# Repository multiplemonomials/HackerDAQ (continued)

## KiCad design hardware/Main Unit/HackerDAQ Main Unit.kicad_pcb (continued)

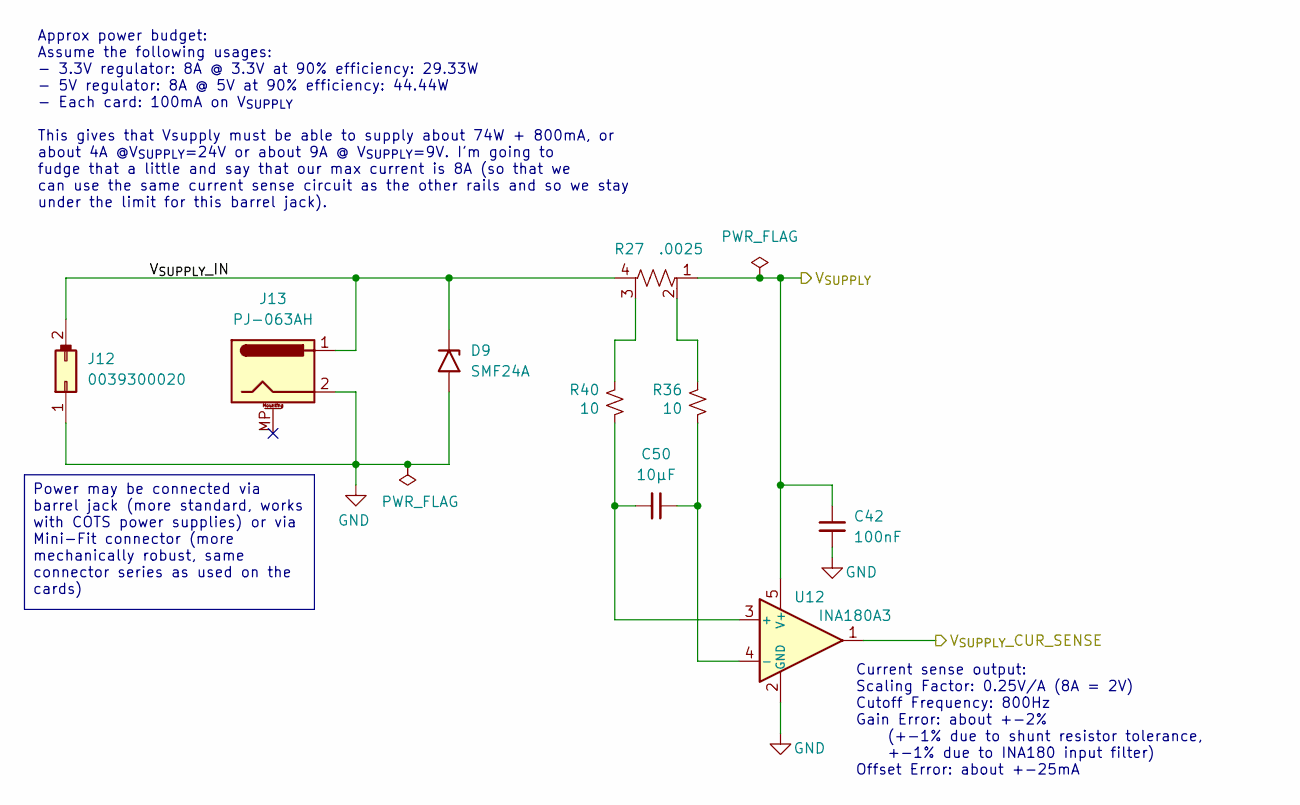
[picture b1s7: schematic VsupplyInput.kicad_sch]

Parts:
C42: 100nF; C_0603_1608Metric
C50: 10µF; C_1206_3216Metric
D9: SMF24A; D_SMF
J12: 0039300020; Molex_Mini-Fit_Jr_5569-02A2_2x01_P4.20mm_Horizontal
J13: PJ-063AH; BarrelJack_CUI_PJ-063AH_Horizontal
R27: .0025; D1FCP0612
R36, R40: 10; R_0603_1608Metric
U12: INA180A3; SOT-23-5

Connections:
/V_{SUPPLY} Input/V_{SUPPLY}_IN: D9.1 (A1), J12.2, J13.1, R27.4
/V_{SUPPLY}_CUR_SENSE: U12.1; also elsewhere on the board
unnamed: R27.2, R36.1
unnamed: R27.3, R40.1
unnamed: C50.2, R40.2, U12.3 (+)
unnamed: C50.1, R36.2, U12.4 (-)
V_{SUPPLY}: C42.1, R27.1, U12.5 (V+); also elsewhere on the board

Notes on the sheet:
Current sense output: Scaling Factor: 0.25V/A (8A = 2V) Cutoff Frequency: 800Hz Gain Error: about +-2% (+-1% due to shunt resistor tolerance, +-1% due to INA180 input filter) Offset Error: about +-25mA
Approx power budget: Assume the following usages: - 3.3V regulator: 8A @ 3.3V at 90% efficiency: 29.33W - 5V regulator: 8A @ 5V at 90% efficiency: 44.44W - Each card: 100mA on V_{SUPPLY} This gives that Vsupply must be able to supply about 74W + 800mA, or about 4A @V_{SUPPLY}=24V or about 9A @ V_{S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
Power may be connected via barrel jack (more standard, works with COTS power supplies) or via Mini-Fit connector (more mechanically robust, same connector series as used on the cards)

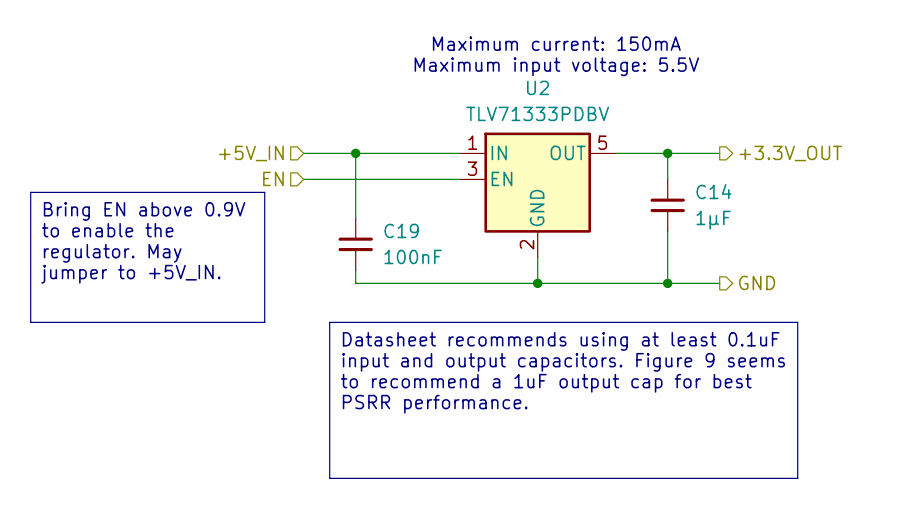
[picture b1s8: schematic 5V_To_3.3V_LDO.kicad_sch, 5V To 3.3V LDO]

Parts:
C14: 1µF; C_0603_1608Metric
C19: 100nF; C_0603_1608Metric
U2: TLV71333PDBV; SOT-23-5

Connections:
/~MCU_RST: U2.3 (EN); also elsewhere on the board

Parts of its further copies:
C3: 1µF; C_0603_1608Metric
C4: 100nF; C_0603_1608Metric

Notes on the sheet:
Maximum current: 150mA Maximum input voltage: 5.5V
Bring EN above 0.9V to enable the regulator. May jumper to +5V_IN.
Datasheet recommends using at least 0.1uF input and output capacitors. Figure 9 seems to recommend a 1uF output cap for best PSRR performance.

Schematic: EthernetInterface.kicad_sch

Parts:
C28, C35: 22µF; C_1210_3225Metric
C29, C31, C34, C44, C45: 100nF; C_0603_1608Metric
C33: 2.2µF; C_1206_3216Metric
D6: ESDS304; SOT-23-5
FB1, FB2: 300@100MHz; R_1206_3216Metric
J11: HFJ11-2450E-L21RL; RJ45_HALO_HFJ11-x2450E-LxxRL_Horizontal-Fixed3DModel
R14, R18: 10k; R_0603_1608Metric
R16, R17, R19, R20: 33; R_0603_1608Metric
R22: 6.49k; R_0603_1608Metric
R52, R53: 270; R_0603_1608Metric
R54: 4.7k; R_0603_1608Metric
U7: KSZ8081RND; QFN-24-1EP_4x4mm_P0.5mm_EP2.6x2.6mm

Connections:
/ETH_RMII.CRS_DV: R17.1, R18.2; also elsewhere on the board
/ETH_RMII.MDC: U7.11 (MDC); also elsewhere on the board
/ETH_RMII.MDIO: U7.10 (MDIO); also elsewhere on the board
/ETH_RMII.RMII_CLK: U7.8 (XI); also elsewhere on the board
/ETH_RMII.RXD0: R19.1; also elsewhere on the board
/ETH_RMII.RXD1: R20.1; also elsewhere on the board
/ETH_RMII.RX_ER: R14.2, R16.1; also elsewhere on the board
/ETH_RMII.TXD0: U7.20 (TXD0); also elsewhere on the board
/ETH_RMII.TXD1: U7.21 (TXD1); also elsewhere on the board
/ETH_RMII.TX_EN: U7.19 (TXEN); also elsewhere on the board
/EthernetInterface/ETH_MDI_RD+: D6.4 (K), J11.3 (RD+), U7.4 (RXP)
/EthernetInterface/ETH_MDI_RD-: D6.5 (K), J11.6 (RD-), U7.3 (RXM)
/EthernetInterface/ETH_MDI_TD+: D6.1 (K), J11.1 (TD+), U7.6 (TXP)
/EthernetInterface/ETH_MDI_TD-: D6.3 (K), J11.2 (TD-), U7.5 (TXM)
/EthernetInterface/KSZ_VDD1.2: C31.1, C33.1, U7.1 (VDD_1.2)
/EthernetInterface/~LED_GREEN: J11.12, R54.1, U7.23 (LED0/ANEN_SPEED)
/~ETH_SPEED_LED: J11.10; also elsewhere on the board
/~MCU_RST: U7.24 (~RST); also elsewhere on the board
unnamed: FB2.1, J11.8, J11.SH
unnamed: J11.9, R52.1
unnamed: J11.11, R53.1
unnamed: C45.1, J11.5 (RCT)
unnamed: C44.1, J11.4 (TCT)
unnamed: R17.2, U7.15 (CRS_DV/PHYAD[1:0])
unnamed: R22.2, U7.9 (REXT)
unnamed: R19.2, U7.13 (RXD0)
unnamed: R20.2, U7.12 (RXD1)
unnamed: R16.2, U7.17 (RXER)
unnamed: C34.1, C35.2, FB1.1, U7.2 (VDDA_3.3)

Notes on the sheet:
Green LED
Yellow LED
LED spec is 2.1V forward voltage @ 10mA. However, the KSZ8081 maxes out at 8mA of LED drive, and the MCU is similar. So, we will shoot for 5mA and assume that the forward voltage will decrease to around 2.0V
Per datasheet, RX_ER should be pulled low for correct operation (I guess it's an undocumented strapping pin?)
Ferrite bead per KSZ8081 reference design
CRS_DV pulled down to low and REF_CLK set high sets the PHY address to 4
Unfortunately there is only one LED pin on this PHY (it defaults to on for link up, flashing for activity). So, we will need to use the MCU to manually control the other (link speed) LED.
This part number of PHY is set up for MCUs like ours that can output a 50MHz clock. This clock is input to the PHY on the XI pin and is used both for the Ethernet signal generation and for the RMII interface. Look ma, no dedicated Ethernet crystal needed!

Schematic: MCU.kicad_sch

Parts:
C5, C7, C8, C10, C16, C17, C18, C19, C20, C21, C23, C26, C27, C36: 100nF; C_0603_1608Metric
C6: 2.2µF; C_1206_3216Metric
C9, C15, C24: 1µF; C_0603_1608Metric
C11: 220nF; C_0603_1608Metric
C13, C14: 10µF; C_1206_3216Metric
D1: AA3528QBS; AA3528
D2: AA3528SURSK; AA3528
D3: ASMB-MTB0-0B3A2; LED_Avago_PLCC4_3.2x2.8mm_CW
D4, D5: BAT54W; SOT-323_SC-70
J1: 3221-10-0300-00
J10: 1x8; PinSocket_1x08_P2.54mm_Vertical
J15: USB4105-GF-A; USB_C_Receptacle_GCT_USB4105-xx-A_16P_TopMnt_Horizontal-Ext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
L1: 1.5µH; L_1210_3225Metric
R1, R4, R7: 30; R_0603_1608Metric
R2, R3: 140; R_0603_1608Metric
R5, R6, R8, R23: 10k; R_0603_1608Metric
R9, R15: 2.2k; R_0603_1608Metric
R43, R44: 5.1k; R_0603_1608Metric
SW1, SW2: MJTP1243; SW_PUSH_1P1T_6x3.5mm_H4.3_APEM_MJTP1243
TP2: VCORE; TestPoint_THTPad_D2.5mm_Drill1.2mm
U5: MCXN547VKLT; LQFP-100-1EP_14x14mm_P0.5mm_EP6.9x6.9mm_Fixed3DModel
U13: USBLC6-2SC6; SOT-23-6
X1: 24.0000MHz; Oscillator_SMD_ECS_2520MV-xxx-xx-4Pin_2.5x2.0mm

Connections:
/+3.3V_CUR_SENSE: U5.22 (P4_0); also elsewhere on the board
/CARD_BUS_0_SPI.CARD_SEL: U5.15 (P2_1); also elsewhere on the board
/CARD_BUS_0_SPI.MISO: U5.19 (P2_5); also elsewhere on the board
/CARD_BUS_0_SPI.MOSI: U5.18 (P2_4); also elsewhere on the board
/CARD_BUS_0_SPI.SCLK: U5.17 (P2_3); also elsewhere on the board
/CARD_BUS_0_SPI.~CS0: U5.16 (P2_2); also elsewhere on the board
/CARD_BUS_0_SPI.~CS1: U5.14 (P2_0); also elsewhere on the board
/CARD_BUS_0_SPI.~CS2: U5.21 (P2_7); also elsewhere on the board
/CARD_BUS_0_SPI.~DRDY: U5.20 (P2_6); also elsewhere on the board
/CARD_BUS_1_SPI.CARD_SEL: U5.91 (P0_23); also elsewhere on the board
/CARD_BUS_1_SPI.MISO: U5.3 (P1_10); also elsewhere on the board
/CARD_BUS_1_SPI.MOSI: U5.1 (P1_8); also elsewhere on the board
/CARD_BUS_1_SPI.SCLK: U5.2 (P1_9); also elsewhere on the board
/CARD_BUS_1_SPI.~CS0: U5.4 (P1_11); also elsewhere on the board
/CARD_BUS_1_SPI.~CS1: U5.90 (P0_22); also elsewhere on the board
/CARD_BUS_1_SPI.~CS2: U5.92 (P1_0); also elsewhere on the board
/CARD_BUS_1_SPI.~DRDY: U5.93 (P1_1); also elsewhere on the board
/CARD_BUS_2_SPI.CARD_SEL: U5.64 (P3_13); also elsewhere on the board
/CARD_BUS_2_SPI.MISO: U5.61 (P3_16); also elsewhere on the board
/CARD_BUS_2_SPI.MOSI: U5.63 (P3_14); also elsewhere on the board
/CARD_BUS_2_SPI.SCLK: U5.62 (P3_15); also elsewhere on the board
/CARD_BUS_2_SPI.~CS0: U5.60 (P3_17); also elsewhere on the board
/CARD_BUS_2_SPI.~CS1: U5.57 (P3_20); also elsewhere on the board
/CARD_BUS_2_SPI.~CS2: U5.56 (P3_21); also elsewhere on the board
/CARD_BUS_2_SPI.~DRDY: U5.75 (P3_0); also elsewhere on the board
/CARD_BUS_3_SPI.CARD_SEL: U5.50 (P5_2); also elsewhere on the board
/CARD_BUS_3_SPI.MISO: U5.69 (P3_9); also elsewhere on the board
/CARD_BUS_3_SPI.MOSI: U5.70 (P3_8); also elsewhere on the board
/CARD_BUS_3_SPI.SCLK: U5.71 (P3_7); also elsewhere on the board
/CARD_BUS_3_SPI.~CS0: U5.65 (P3_12); also elsewhere on the board
/CARD_BUS_3_SPI.~CS1: U5.78 (P0_2); also elsewhere on the board
/CARD_BUS_3_SPI.~CS2: U5.79 (P0_3); also elsewhere on the board
/CARD_BUS_3_SPI.~DRDY: U5.51 (P5_3); also elsewhere on the board
/Card Bus Connectors0/~RESET: U5.27 (P4_5); also elsewhere on the board
/Card Bus Connectors0/~SYNC: U5.28 (P4_6); also elsewhere on the board
/DBG_UART.MCU_RX: U5.35 (P4_12); also elsewhere on the board
/DBG_UART.MCU_TX: U5.36 (P4_13); also elsewhere on the board
/ETH_RMII.CRS_DV: U5.6 (P1_13); also elsewhere on the board
/ETH_RMII.MDC: U5.94 (P1_2); also elsewhere on the board
/ETH_RMII.MDIO: R15.2, U5.95 (P1_3); also elsewhere on the board
/ETH_RMII.RMII_CLK: U5.97 (P1_4); also elsewhere on the board
/ETH_RMII.RXD0: U5.7 (P1_14); also elsewhere on the board
/ETH_RMII.RXD1: U5.8 (P1_15); also elsewhere on the board
/ETH_RMII.RX_ER: U5.5 (P1_12); also elsewhere on the board
/ETH_RMII.TXD0: U5.99 (P1_6); also elsewhere on the board
/ETH_RMII.TXD1: U5.100 (P1_7); also elsewhere on the board
/ETH_RMII.TX_EN: U5.98 (P1_5); also elsewhere on the board
/MCU/+5V_CUR_SENSE: U5.23 (P4_1); also elsewhere on the board
/MCU/CLK_24MHZ: U5.10 (EXTAL48M/P1_31), X1.3 (OUT)
/MCU/ERROR_LED: R2.2, U5.26 (P4_4)
/MCU/MCU_P0_4: J10.1, U5.80 (P0_4)
/MCU/MCU_P0_5: J10.2, U5.81 (P0_5)
/MCU/MCU_P0_16: J10.3, U5.84 (P0_16)
/MCU/MCU_P0_17: J10.4, U5.85 (P0_17)
/MCU/MCU_P0_18: J10.5, U5.86 (P0_18)
/MCU/MCU_P0_19: J10.6, U5.87 (P0_19)
/MCU/MCU_P0_20: J10.7, U5.88 (P0_20)
/MCU/MCU_P0_21: J10.8, U5.89 (P0_21)
/MCU/PREFILT_USBMCU_D+: J15.A6 (D+), J15.B6 (D+), U13.3 (I/O2)
/MCU/PREFILT_USBMCU_D-: J15.A7 (D-), J15.B7 (D-), U13.1 (I/O1)
/MCU/RGB_LED_~B: R7.2, U5.39 (P4_17)
/MCU/RGB_LED_~G: R4.2, U5.38 (P4_16)
/MCU/RGB_LED_~R: R3.2, U5.37 (P4_15)
/MCU/STATUS_LED: R1.1, U5.25 (P4_3)
/MCU/SWCLK: J1.4, R5.2, U5.77 (SWCLK/P0_1/TCLK)
/MCU/SWDIO: J1.2, R6.1, U5.76 (SWDIO/P0_0/TMS)
/MCU/USBMCU_D+: U5.40 (USB1_DP), U13.4 (I/O2)
/MCU/USBMCU_D-: U5.41 (USB1_DM), U13.6 (I/O1)
/MCU/USBMCU_VBUS: J15.A4 (VBUS), J15.A9 (VBUS), J15.B4 (VBUS), J15.B9 (VBUS), U5.42 (USB1_VBUS), U13.5 (VBUS)
/MCU/VCORE: C13.2, C16.1, C20.1, L1.2, TP2.1 (1_1), U5.12 (VDD_CORE), U5.58 (VDD_CORE)
/MCU/VDD_SYS: C6.1, U5.55 (VDD_SYS)
/MCU/~ISPMODE: C36.1, D5.1 (A), R23.1, SW2.2, U5.82 (ISPMODE_N/P0_6)
/V_{SUPPLY}_CUR_SENSE: U5.24 (P4_2); also elsewhere on the board
/uSD_SPI.MISO: U5.68 (P3_10); also elsewhere on the board
/uSD_SPI.MOSI: U5.74 (P3_1); also elsewhere on the board
/uSD_SPI.SCLK: U5.72 (P3_6); also elsewhere on the board
/uSD_SPI.~CS: U5.67 (P3_11); also elsewhere on the board
/~ETH_SPEED_LED: U5.48 (P5_0); also elsewhere on the board
/~MCU_RST: C5.1, D4.1 (A), J1.10, R8.1, R9.1, SW1.2; also elsewhere on the board
/~SD_CARD_EN: U5.49 (P5_1); also elsewhere on the board
unnamed: D1.2 (A), R1.2
unnamed: D2.2 (A), R2.1
unnamed: D3.2 (BK), R7.1
unnamed: D3.3 (GK), R4.1
unnamed: D3.4 (RK), R3.1
unnamed: J15.A5 (CC1), R43.2
unnamed: J15.B5 (CC2), R44.2
unnamed: L1.1, U5.53 (DCDC_LX)
unnamed: C11.1, U5.29 (P4_7/VREFI/VREFO)
unnamed: R9.2, U5.9 (RESET_B)

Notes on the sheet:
RTCK
GNDDetect
TMS/SWDIO
VTREF
~RST
Route per hardware design guide:
Expansion Header
GND
TDI
TDO/SWO
TCLK/SWCLK
Reset circuit. Can be pulled low from the pushbutton or the JTAG connector. Also pulled low at startup by the MCU during its power-on reset. The diode exists to discharge the capacitor when power is turned off.
Note: Decoupling per hardware design guide. Generally each group of pins gets one large capacitor, and each pin gets a smaller capacitor
Main CPU clock source. Yeah we could get away with using the internal oscillator to drive the CPU core, but it's not accurate enough for Ethernet so we'd still need a crystal oscillator. So why not plonk down a TCXO and enjoy +-5ppm accurate clocks for everything?
Using the remaining 5 free GPIOs for indicator LEDs
Per datasheet VDD_P4 and VDD_ANA must be powered by the same supply.
SWD debug connector. Not using JTAG as it's not worth the two extra pins for no additional benefit. Resistors on SWDIO and SWCLK are per hardware design guide recommendation.
This tricolor LED specifies V_{F} = 2.1V (red) and 3.1V (green and blue) @ 20mA. Making a ballpark assumption that the forward voltage decreases by 0.1V if we reduce the forward current to 10mA.
ISP mode circuit. Button can be pressed to force the MCU to boot into ISP (recovery) mode.

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
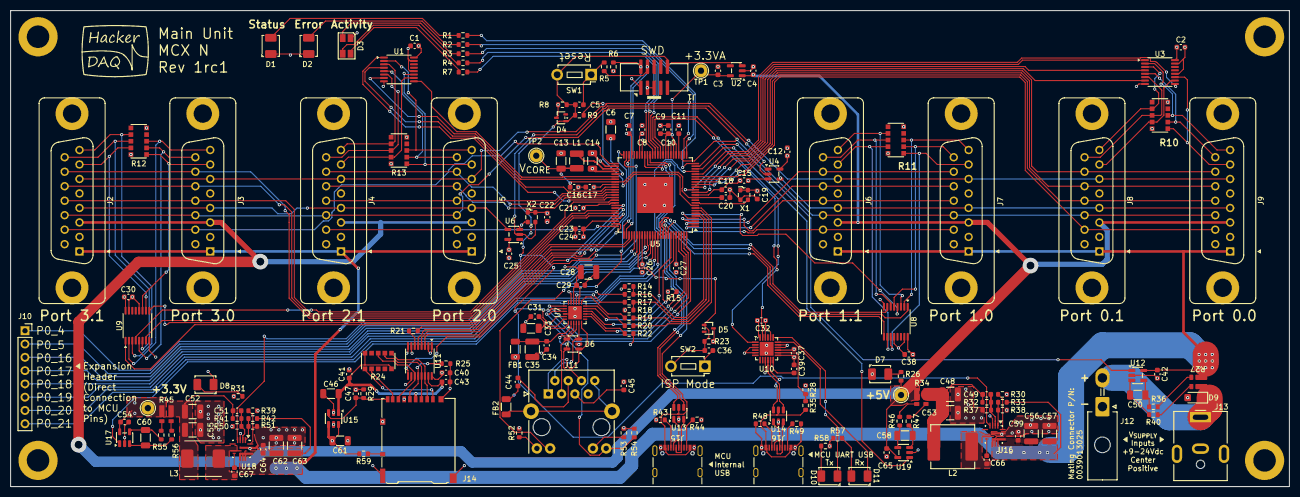
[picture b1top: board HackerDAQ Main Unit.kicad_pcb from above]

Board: 4 copper layers, 244.5 x 91.0 mm, 190 parts (0 on the bottom side), 189 nets.

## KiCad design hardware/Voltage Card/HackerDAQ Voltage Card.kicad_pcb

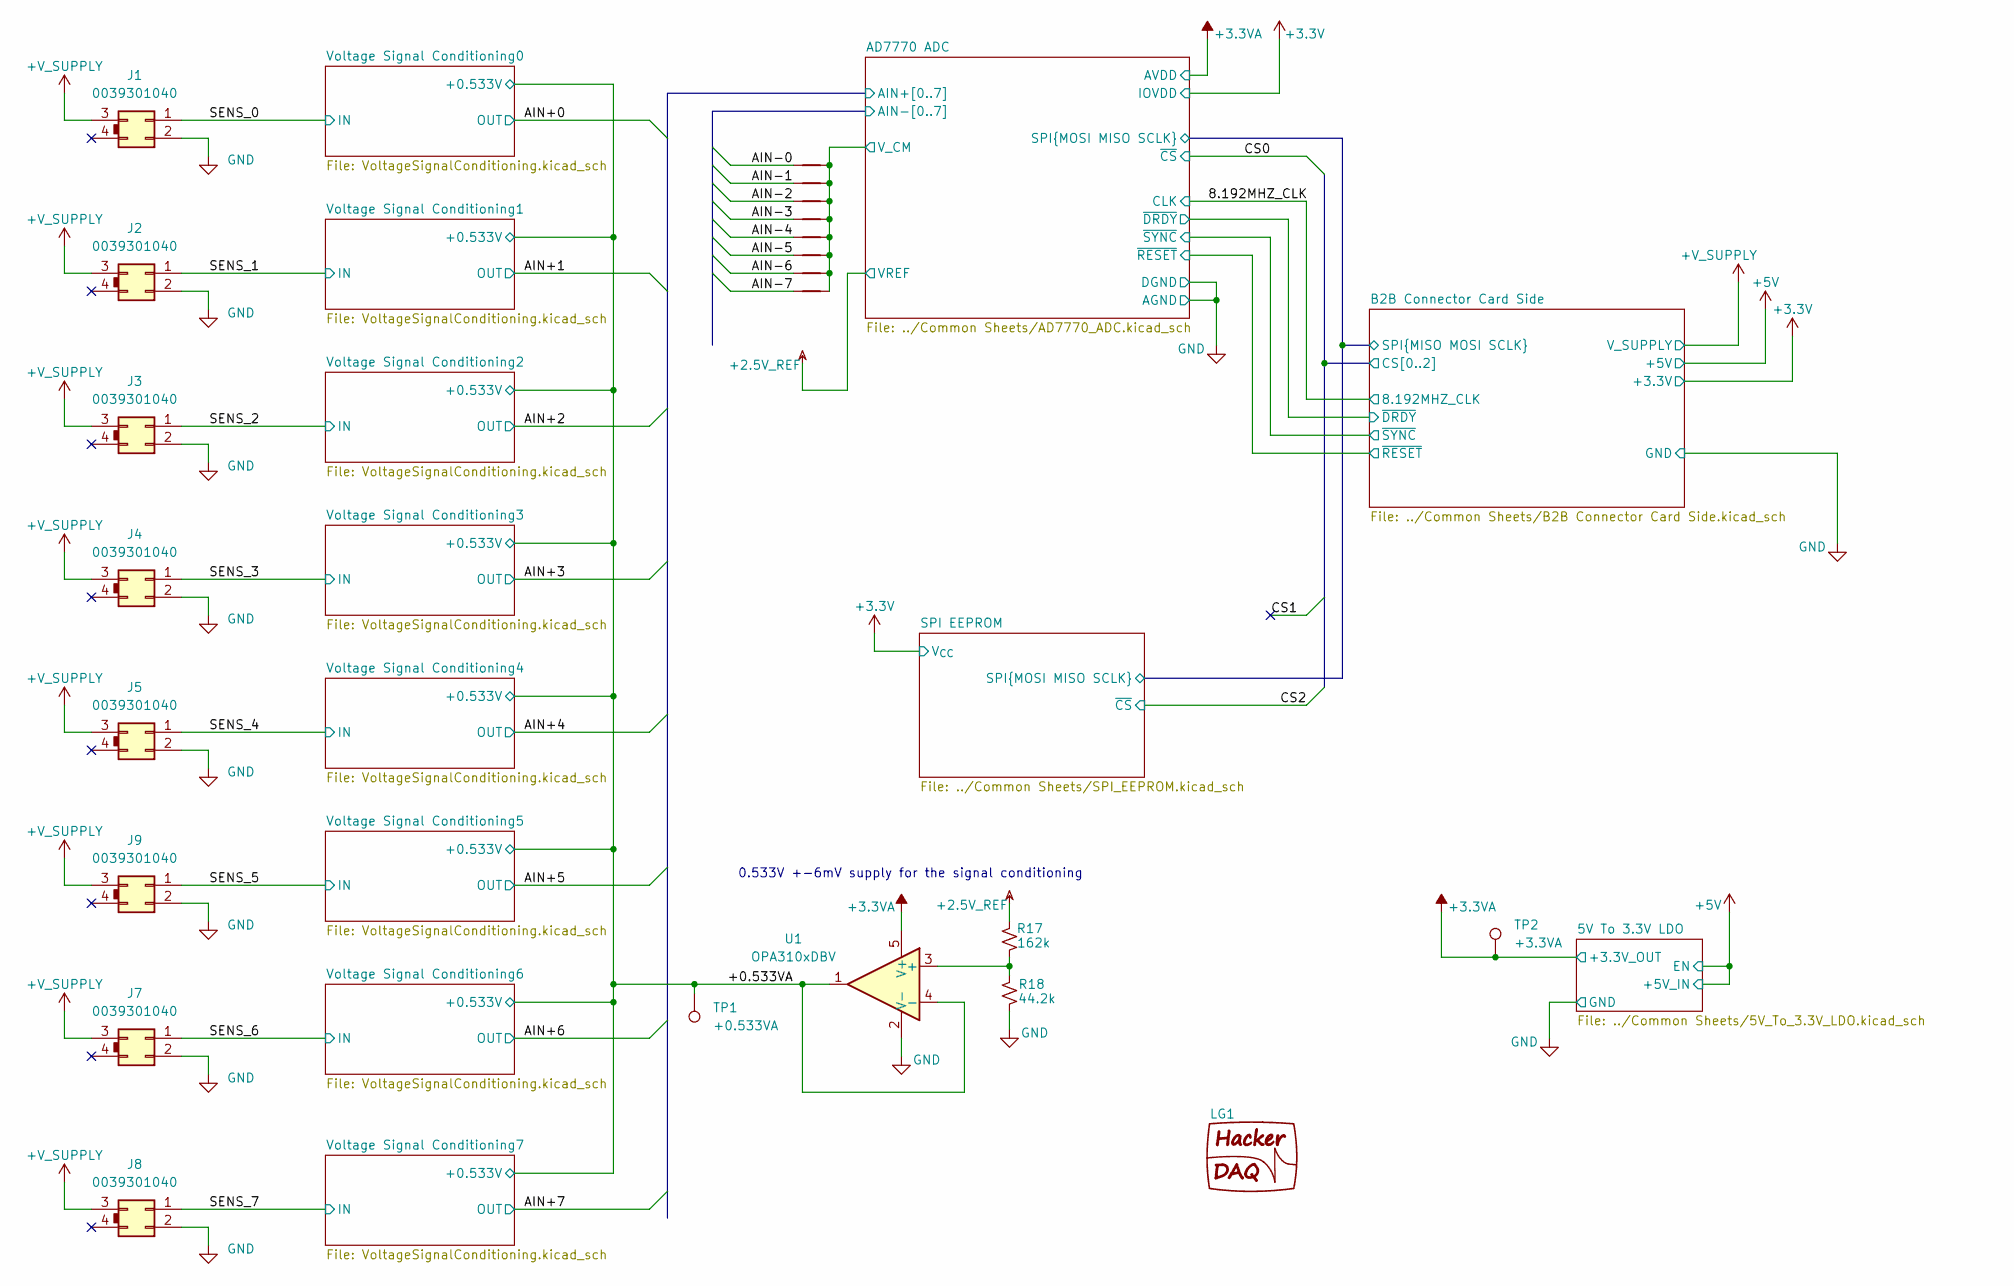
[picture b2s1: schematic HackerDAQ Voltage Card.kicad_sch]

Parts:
J1, J2, J3, J4, J5, J7, J8, J9: 0039301040; Molex_Mini-Fit_Jr_5569-04A2_2x02_P4.20mm_Horizontal
LG1: HackerDAQ Logo
NT1, NT2, NT3, NT4, NT5, NT6, NT7, NT8: NetTie_2; NetTie-2_SMD_Pad0.2mm
R17: 162k; R_0603_1608Metric
R18: 44.2k; R_0603_1608Metric
TP1: +0.533VA; TestPoint_THTPad_D2.5mm_Drill1.2mm
TP2: +3.3VA; TestPoint_THTPad_D2.5mm_Drill1.2mm
U1: OPA310xDBV; SOT-23-5

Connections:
+2.5V_REF: R17.1; also elsewhere on the board
+3.3VA: TP2.1 (1_1), U1.5 (V+); also elsewhere on the board
+V_SUPPLY: J1.3, J2.3, J3.3, J4.3, J5.3, J7.3, J8.3, J9.3; also elsewhere on the board
/+0.533VA: TP1.1 (1_1), U1.1, U1.4 (-); also elsewhere on the board
/AD7770 ADC/AIN-0: NT1.1; also elsewhere on the board
/AD7770 ADC/AIN-1: NT3.1; also elsewhere on the board
/AD7770 ADC/AIN-2: NT5.1; also elsewhere on the board
/AD7770 ADC/AIN-3: NT7.1; also elsewhere on the board
/AD7770 ADC/AIN-4: NT2.1; also elsewhere on the board
/AD7770 ADC/AIN-5: NT4.1; also elsewhere on the board
/AD7770 ADC/AIN-6: NT6.1; also elsewhere on the board
/AD7770 ADC/AIN-7: NT8.1; also elsewhere on the board
/AD7770 ADC/V_CM: NT1.2, NT2.2, NT3.2, NT4.2, NT5.2, NT6.2, NT7.2, NT8.2; also elsewhere on the board
/SENS_0: J1.1; also elsewhere on the board
/SENS_1: J2.1; also elsewhere on the board
/SENS_2: J3.1; also elsewhere on the board
/SENS_3: J4.1; also elsewhere on the board
/SENS_4: J5.1; also elsewhere on the board
/SENS_5: J9.1; also elsewhere on the board
/SENS_6: J7.1; also elsewhere on the board
/SENS_7: J8.1; also elsewhere on the board
GND: J1.2, J2.2, J3.2, J4.2, J5.2, J7.2, J8.2, J9.2, R18.2, U1.2 (V-); also elsewhere on the board
unnamed: R17.2, R18.1, U1.3 (+)

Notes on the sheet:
0.533V +-6mV supply for the signal conditioning

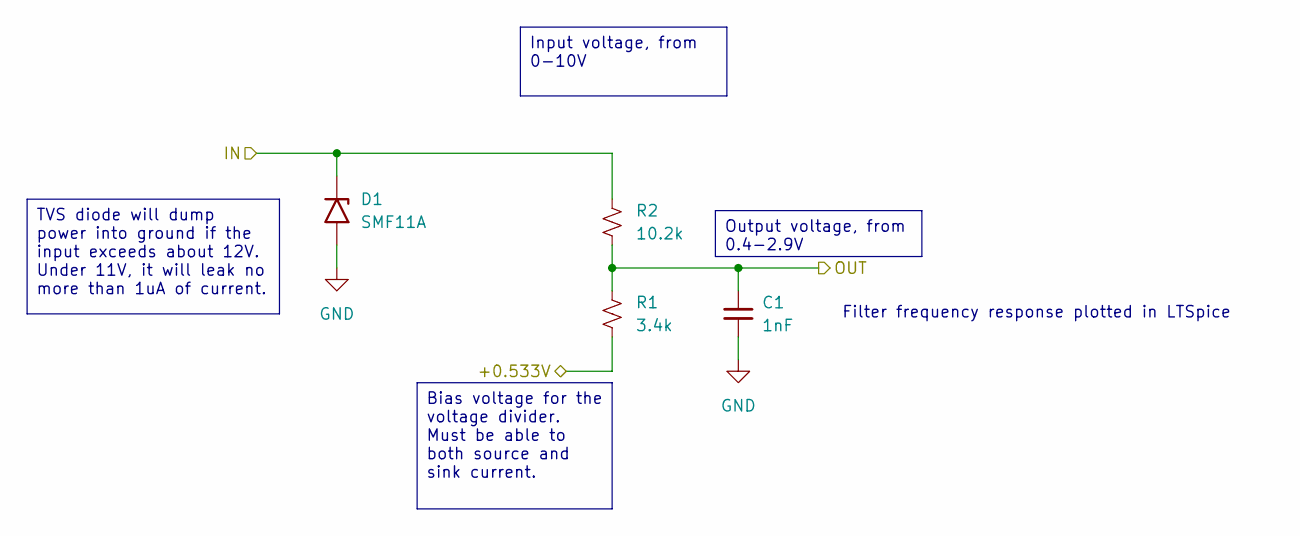
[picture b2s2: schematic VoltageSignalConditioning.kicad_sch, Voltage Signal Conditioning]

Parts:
C1: 1nF; C_0603_1608Metric
D1: SMF11A; D_SMF
R1: 3.4k; R_0603_1608Metric
R2: 10.2k; R_0603_1608Metric

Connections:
/+0.533VA: R1.2; also elsewhere on the board
/AD7770 ADC/AIN+0: C1.1, R1.1, R2.2; also elsewhere on the board
/SENS_0: D1.1 (A1), R2.1; also elsewhere on the board
GND: C1.2, D1.2 (A2); also elsewhere on the board

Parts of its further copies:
C2, C3, C4, C6, C7, C8, C31: 1nF; C_0603_1608Metric
D2, D3, D4, D5, D6, D7, D8: SMF11A; D_SMF
R3, R5, R7, R9, R11, R13, R15: 3.4k; R_0603_1608Metric
R4, R6, R8, R10, R12, R14, R16: 10.2k; R_0603_1608Metric

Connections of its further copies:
/+0.533VA: R3.2, R5.2, R7.2, R9.2, R11.2, R13.2, R15.2; also elsewhere on the board
/AD7770 ADC/AIN+1: C2.1, R3.1, R4.2; also elsewhere on the board
/AD7770 ADC/AIN+2: C3.1, R5.1, R6.2; also elsewhere on the board
/AD7770 ADC/AIN+3: C4.1, R7.1, R8.2; also elsewhere on the board
/AD7770 ADC/AIN+4: C31.1, R9.1, R10.2; also elsewhere on the board
/AD7770 ADC/AIN+5: C6.1, R11.1, R12.2; also elsewhere on the board
/AD7770 ADC/AIN+6: C7.1, R13.1, R14.2; also elsewhere on the board
/AD7770 ADC/AIN+7: C8.1, R15.1, R16.2; also elsewhere on the board
/SENS_1: D2.1 (A1), R4.1; also elsewhere on the board
/SENS_2: D3.1 (A1), R6.1; also elsewhere on the board
/SENS_3: D4.1 (A1), R8.1; also elsewhere on the board
/SENS_4: D5.1 (A1), R10.1; also elsewhere on the board
/SENS_5: D6.1 (A1), R12.1; also elsewhere on the board
/SENS_6: D7.1 (A1), R14.1; also elsewhere on the board
/SENS_7: D8.1 (A1), R16.1; also elsewhere on the board
GND: C2.2, C3.2, C4.2, C6.2, C7.2, C8.2, C31.2, D2.2 (A2), D3.2 (A2), D4.2 (A2), D5.2 (A2), D6.2 (A2), D7.2 (A2), D8.2 (A2); also elsewhere on the board

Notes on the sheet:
Filter frequency response plotted in LTSpice
Output voltage, from 0.4-2.9V
Input voltage, from 0-10V
Bias voltage for the voltage divider. Must be able to both source and sink current.
TVS diode will dump power into ground if the input exceeds about 12V. Under 11V, it will leak no more than 1uA of current.

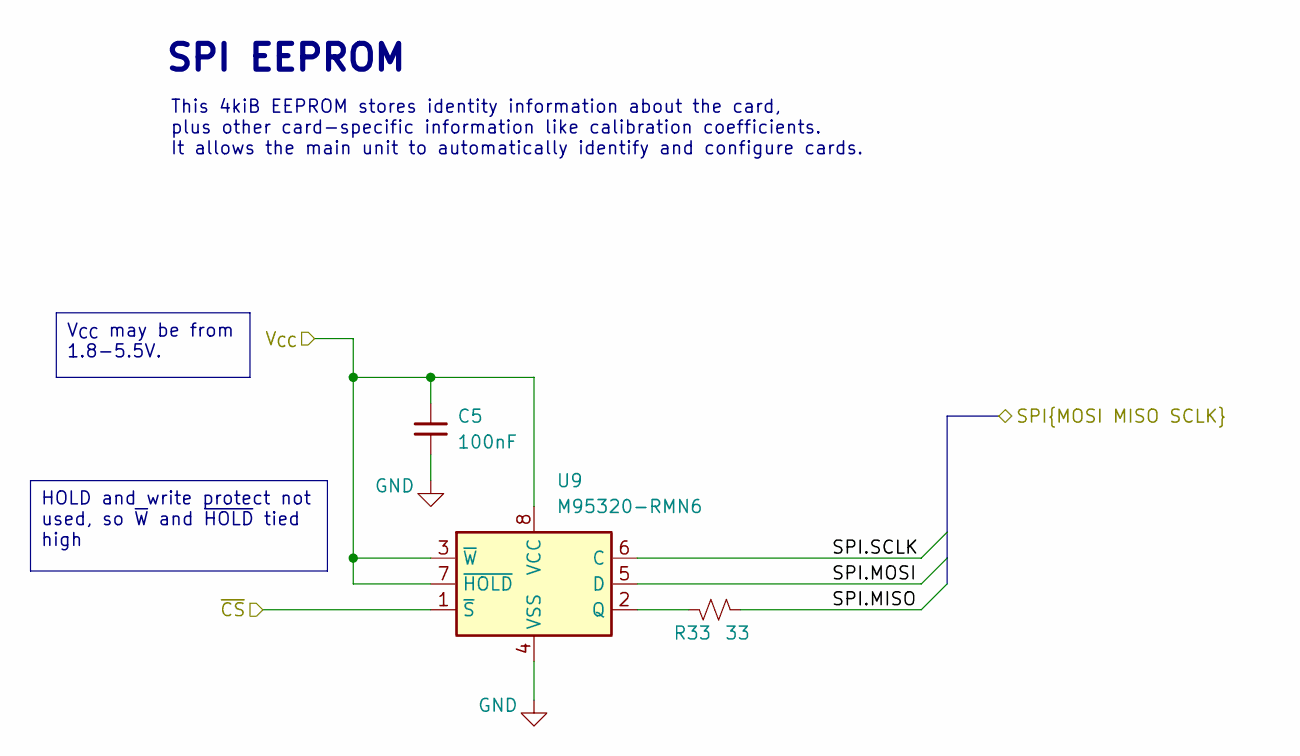
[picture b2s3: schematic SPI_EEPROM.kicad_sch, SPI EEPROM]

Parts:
C5: 100nF; C_0603_1608Metric
R33: 33; R_0603_1608Metric
U9: M95320-RMN6; SOIC-8_3.9x4.9mm_P1.27mm

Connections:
+3.3V: C5.1, U9.3 (~W), U9.7 (~HOLD), U9.8 (VCC); also elsewhere on the board
/AD7770 ADC/SPI.MISO: R33.2; also elsewhere on the board
/AD7770 ADC/SPI.MOSI: U9.5 (D); also elsewhere on the board
/AD7770 ADC/SPI.SCLK: U9.6 (C); also elsewhere on the board
/B2B Connector Card Side/CS2: U9.1 (~S); also elsewhere on the board
GND: C5.2, U9.4 (VSS); also elsewhere on the board
unnamed: R33.1, U9.2 (Q)

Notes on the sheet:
SPI EEPROM
This 4kiB EEPROM stores identity information about the card, plus other card-specific information like calibration coefficients. It allows the main unit to automatically identify and configure cards.
HOLD and write protect not used, so ~{W} and ~{HOLD} tied high
V_{CC} may be from 1.8-5.5V.

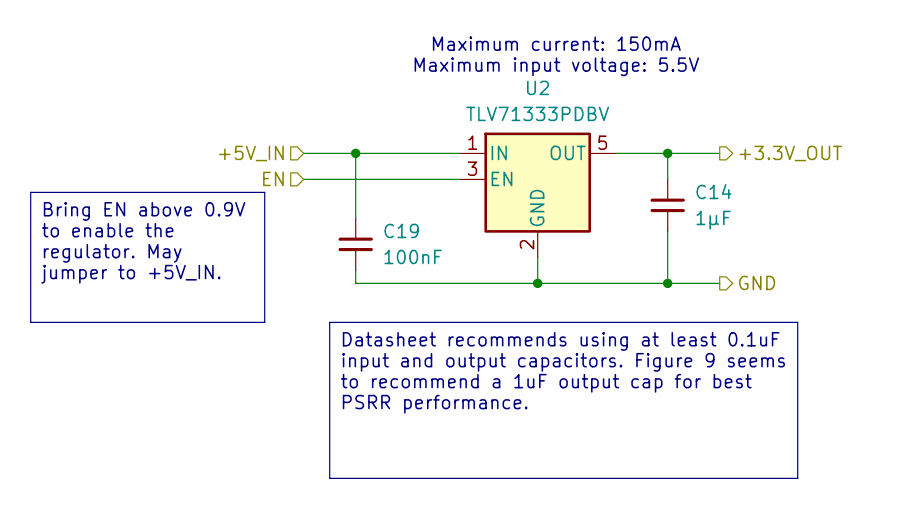
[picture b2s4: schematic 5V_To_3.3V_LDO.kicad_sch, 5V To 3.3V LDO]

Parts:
C14: 1µF; C_0603_1608Metric
C19: 100nF; C_0603_1608Metric
U2: TLV71333PDBV; SOT-23-5

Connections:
+3.3VA: C14.1, U2.5 (OUT); also elsewhere on the board
+5V: C19.1, U2.1 (IN), U2.3 (EN); also elsewhere on the board
GND: C14.2, C19.2, U2.2 (GND); also elsewhere on the board

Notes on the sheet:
Maximum current: 150mA Maximum input voltage: 5.5V
Bring EN above 0.9V to enable the regulator. May jumper to +5V_IN.
Datasheet recommends using at least 0.1uF input and output capacitors. Figure 9 seems to recommend a 1uF output cap for best PSRR performance.

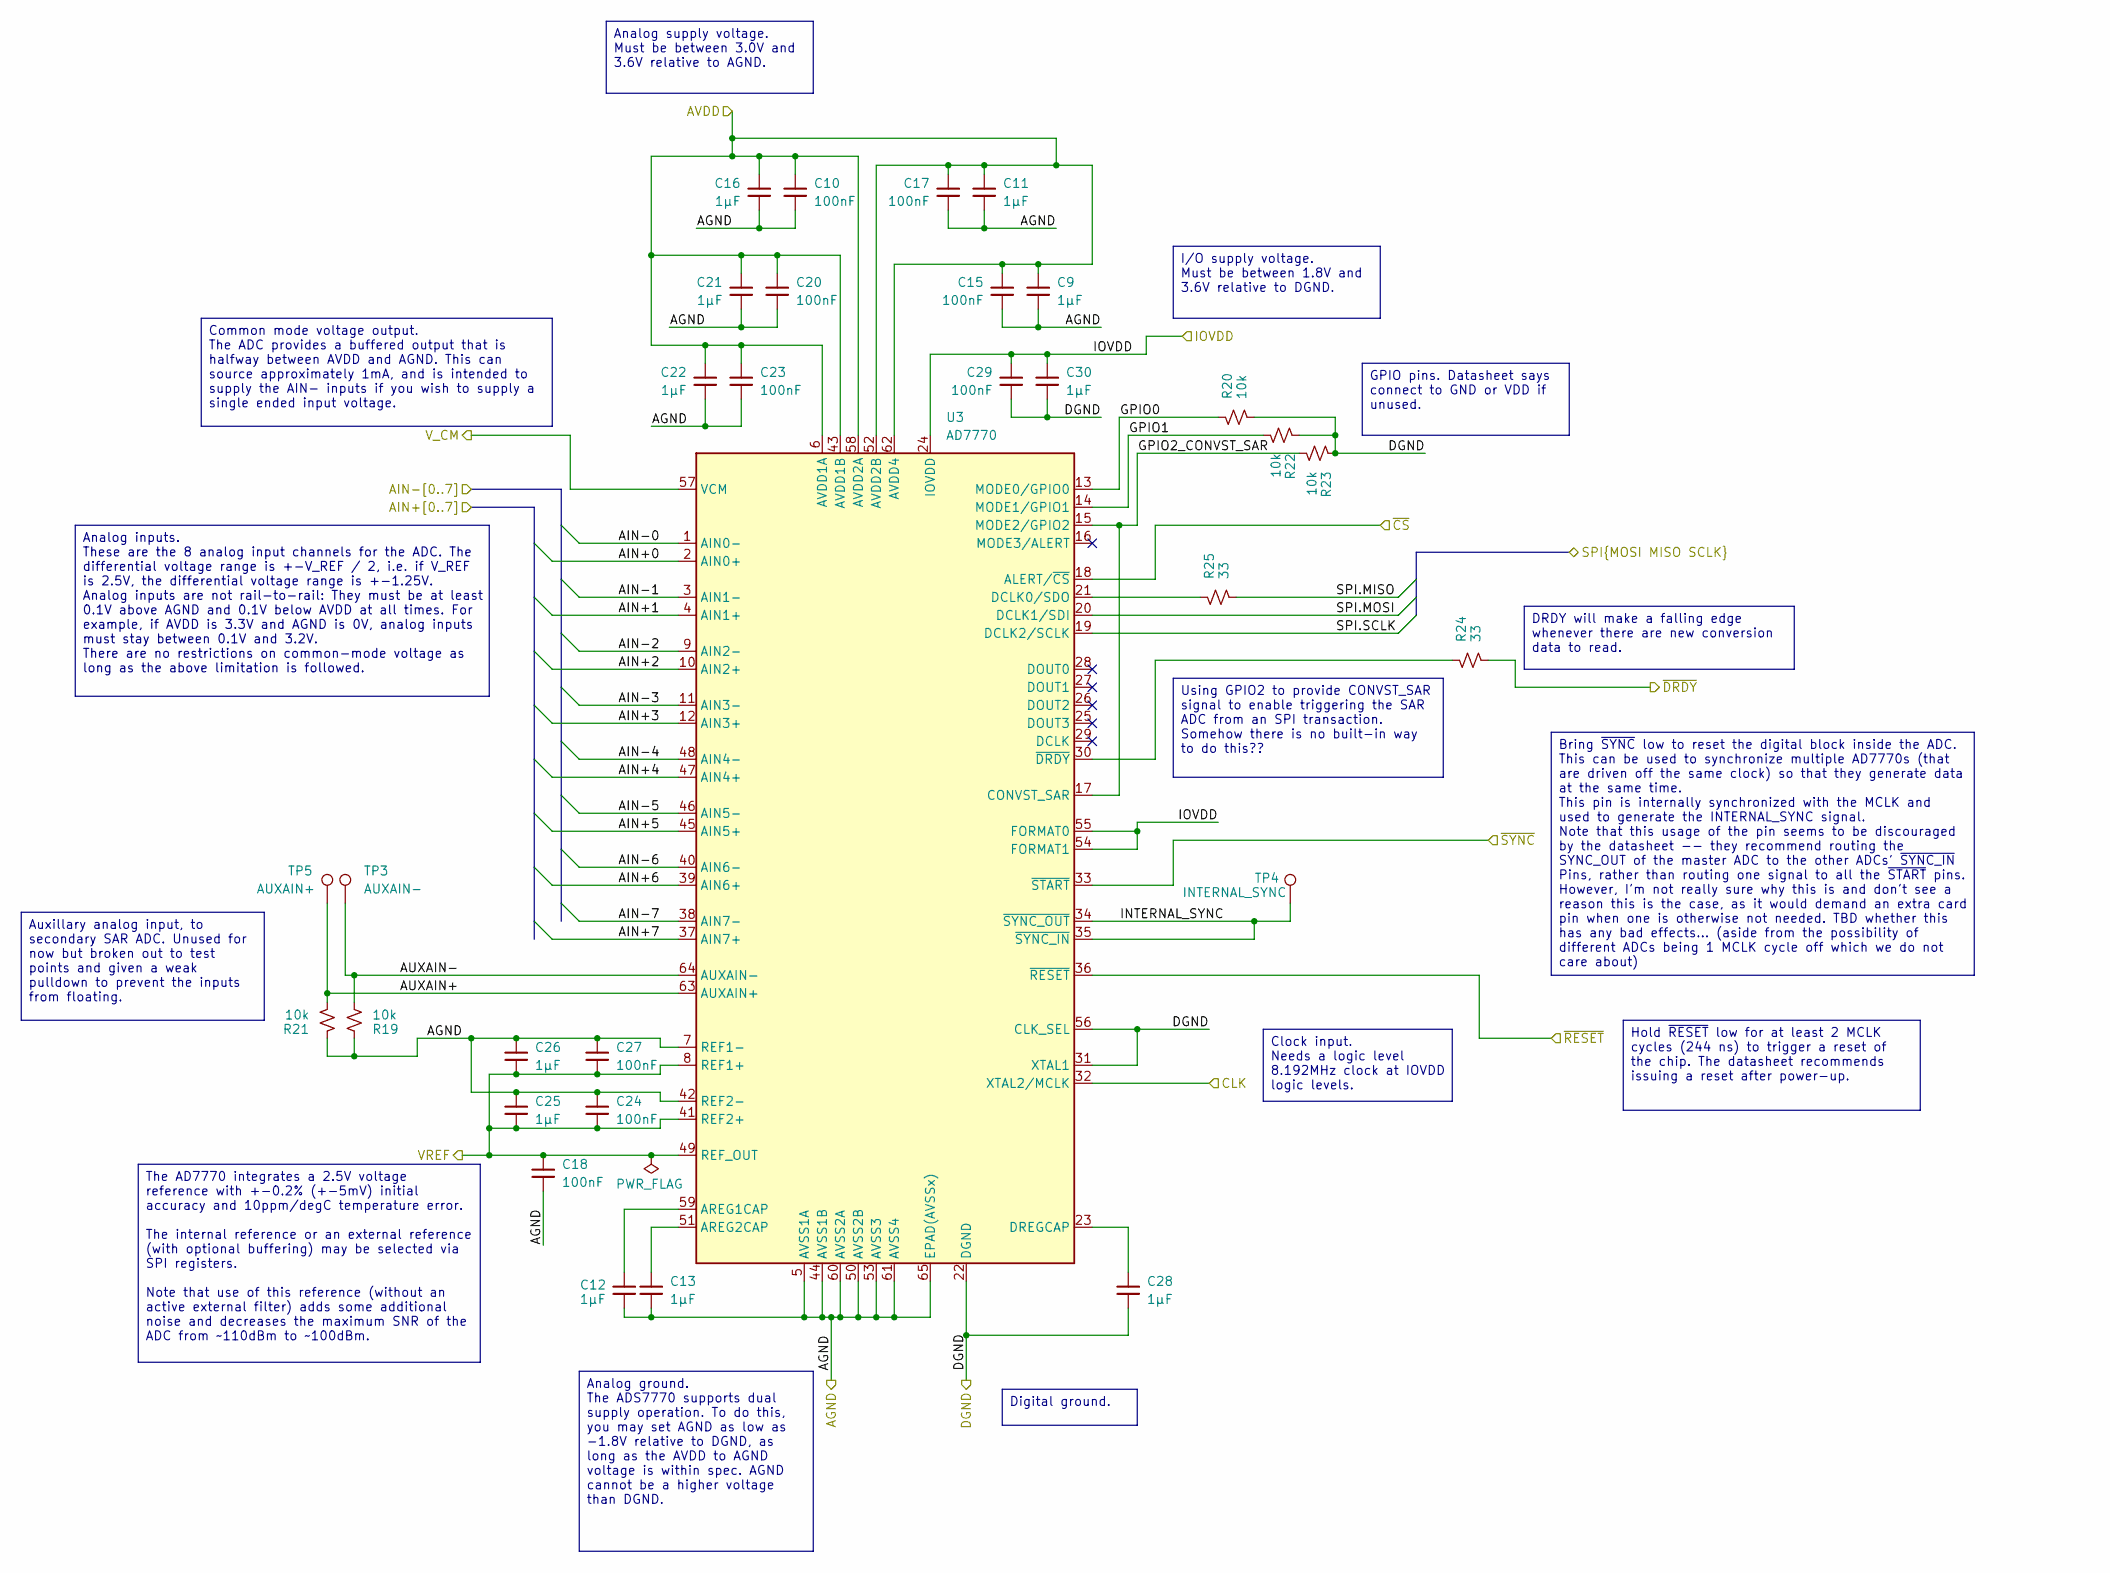
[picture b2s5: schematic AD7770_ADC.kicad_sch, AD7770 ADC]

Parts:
C9, C11, C12, C13, C16, C21, C22, C25, C26, C28, C30: 1µF; C_0603_1608Metric
C10, C15, C17, C18, C20, C23, C24, C27, C29: 100nF; C_0603_1608Metric
R19, R20, R21, R22, R23: 10k; R_0603_1608Metric
R24, R25: 33; R_0603_1608Metric
TP3: AUXAIN-; TestPoint_THTPad_D2.5mm_Drill1.2mm
TP4: INTERNAL_SYNC; TestPoint_THTPad_D2.5mm_Drill1.2mm
TP5: AUXAIN+; TestPoint_THTPad_D2.5mm_Drill1.2mm
U3: AD7770; LFCSP-64-1EP_9x9mm_P0.5mm_EP5.21x5.21mm_LeadsExtended

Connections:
+2.5V_REF: C18.1, C24.2, C25.2, C26.2, C27.2, U3.8 (REF1+), U3.41 (REF2+), U3.49 (REF_OUT); also elsewhere on the board
+3.3V: C29.1, C30.1, U3.24 (IOVDD), U3.54 (FORMAT1), U3.55 (FORMAT0); also elsewhere on the board
+3.3VA: C9.1, C10.1, C11.1, C15.1, C16.1, C17.1, C20.1, C21.1, C22.1, C23.1, U3.6 (AVDD1A), U3.43 (AVDD1B), U3.52 (AVDD2B), U3.58 (AVDD2A), U3.62 (AVDD4); also elsewhere on the board
/8.192MHZ_CLK: U3.32 (XTAL2/MCLK); also elsewhere on the board
/AD7770 ADC/AIN+0: U3.2 (AIN0+); also elsewhere on the board
/AD7770 ADC/AIN+1: U3.4 (AIN1+); also elsewhere on the board
/AD7770 ADC/AIN+2: U3.10 (AIN2+); also elsewhere on the board
/AD7770 ADC/AIN+3: U3.12 (AIN3+); also elsewhere on the board
/AD7770 ADC/AIN+4: U3.47 (AIN4+); also elsewhere on the board
/AD7770 ADC/AIN+5: U3.45 (AIN5+); also elsewhere on the board
/AD7770 ADC/AIN+6: U3.39 (AIN6+); also elsewhere on the board
/AD7770 ADC/AIN+7: U3.37 (AIN7+); also elsewhere on the board
/AD7770 ADC/AIN-0: U3.1 (AIN0-); also elsewhere on the board
/AD7770 ADC/AIN-1: U3.3 (AIN1-); also elsewhere on the board
/AD7770 ADC/AIN-2: U3.9 (AIN2-); also elsewhere on the board
/AD7770 ADC/AIN-3: U3.11 (AIN3-); also elsewhere on the board
/AD7770 ADC/AIN-4: U3.48 (AIN4-); also elsewhere on the board
/AD7770 ADC/AIN-5: U3.46 (AIN5-); also elsewhere on the board
/AD7770 ADC/AIN-6: U3.40 (AIN6-); also elsewhere on the board
/AD7770 ADC/AIN-7: U3.38 (AIN7-); also elsewhere on the board
/AD7770 ADC/AUXAIN+: R21.2, TP5.1 (1_1), U3.63 (AUXAIN+)
/AD7770 ADC/AUXAIN-: R19.2, TP3.1 (1_1), U3.64 (AUXAIN-)
/AD7770 ADC/GPIO0: R20.1, U3.13 (MODE0/GPIO0)
/AD7770 ADC/GPIO1: R22.2, U3.14 (MODE1/GPIO1)
/AD7770 ADC/GPIO2_CONVST_SAR: R23.2, U3.15 (MODE2/GPIO2), U3.17 (CONVST_SAR)
/AD7770 ADC/INTERNAL_SYNC: TP4.1 (1_1), U3.34 (~SYNC_OUT), U3.35 (~SYNC_IN)
/AD7770 ADC/SPI.MISO: R25.2; also elsewhere on the board
/AD7770 ADC/SPI.MOSI: U3.20 (DCLK1/SDI); also elsewhere on the board
/AD7770 ADC/SPI.SCLK: U3.19 (DCLK2/SCLK); also elsewhere on the board
/AD7770 ADC/V_CM: U3.57 (VCM); also elsewhere on the board
/AD7770 ADC/~DRDY: R24.2; also elsewhere on the board
/AD7770 ADC/~RESET: U3.36 (~RESET); also elsewhere on the board
/AD7770 ADC/~SYNC: U3.33 (~START); also elsewhere on the board
/B2B Connector Card Side/CS0: U3.18 (ALERT/~CS); also elsewhere on the board
GND: C9.2, C10.2, C11.2, C12.2, C13.2, C15.2, C16.2, C17.2, C18.2, C20.2, C21.2, C22.2, C23.2, C24.1, C25.1, C26.1, C27.1, C28.2, C29.2, C30.2, R19.1, R20.2, R21.1, R22.1, R23.1, U3.5 (AVSS1A), U3.7 (REF1-), U3.22 (DGND), U3.31 (XTAL1), U3.42 (REF2-), U3.44 (AVSS1B), U3.50 (AVSS2B), U3.53 (AVSS3), U3.56 (CLK_SEL), U3.60 (AVSS2A), U3.61 (AVSS4), U3.65 (EPAD(AVSSx)); also elsewhere on the board
unnamed: C12.1, U3.59 (AREG1CAP)
unnamed: C13.1, U3.51 (AREG2CAP)
unnamed: R25.1, U3.21 (DCLK0/SDO)
unnamed: C28.1, U3.23 (DREGCAP)
unnamed: R24.1, U3.30 (~DRDY)

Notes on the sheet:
Analog inputs. These are the 8 analog input channels for the ADC. The differential voltage range is +-V_REF / 2, i.e. if V_REF is 2.5V, the differential voltage range is +-1.25V. Analog inputs are not rail-to-rail: They must be at least 0.1V above AGND and 0.1V below AVDD at all times. For example,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
Digital ground.
GPIO pins. Datasheet says connect to GND or VDD if unused.
Bring ~{SYNC} low to reset the digital block inside the ADC. This can be used to synchronize multiple AD7770s (that are driven off the same clock) so that they generate data at the same time. This pin is internally synchronized with the MCLK and used to generate the INTERNAL_SYNC signal. Note that 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
Auxillary analog input, to secondary SAR ADC. Unused for now but broken out to test points and given a weak pulldown to prevent the inputs from floating.
Using GPIO2 to provide CONVST_SAR signal to enable triggering the SAR ADC from an SPI transaction. Somehow there is no built-in way to do this??
The AD7770 integrates a 2.5V voltage reference with +-0.2% (+-5mV) initial accuracy and 10ppm/degC temperature error. The internal reference or an external reference (with optional buffering) may be selected via SPI registers. Note that use of this reference (without an active external filter) adds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
Clock input. Needs a logic level 8.192MHz clock at IOVDD logic levels.
Analog supply voltage. Must be between 3.0V and 3.6V relative to AGND.
Common mode voltage output. The ADC provides a buffered output that is halfway between AVDD and AGND. This can source approximately 1mA, and is intended to supply the AIN- inputs if you wish to supply a single ended input voltage.
DRDY will make a falling edge whenever there are new conversion data to read.
Analog ground. The ADS7770 supports dual supply operation. To do this, you may set AGND as low as -1.8V relative to DGND, as long as the AVDD to AGND voltage is within spec. AGND cannot be a higher voltage than DGND.
I/O supply voltage. Must be between 1.8V and 3.6V relative to DGND.
Hold ~{RESET} low for at least 2 MCLK cycles (244 ns) to trigger a reset of the chip. The datasheet recommends issuing a reset after power-up.
